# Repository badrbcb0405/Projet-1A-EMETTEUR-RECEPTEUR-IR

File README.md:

# Projet-1A-EMETTEUR-RECEPTEUR-IR

Ce depot contient les deux projets KiCad et la partie du développement informatique sur STM32 CubeIDE:

- KICAD_EMETTEUR_PCB_final (1)
- KICAD RECEPTEUR FINAL2 (2)

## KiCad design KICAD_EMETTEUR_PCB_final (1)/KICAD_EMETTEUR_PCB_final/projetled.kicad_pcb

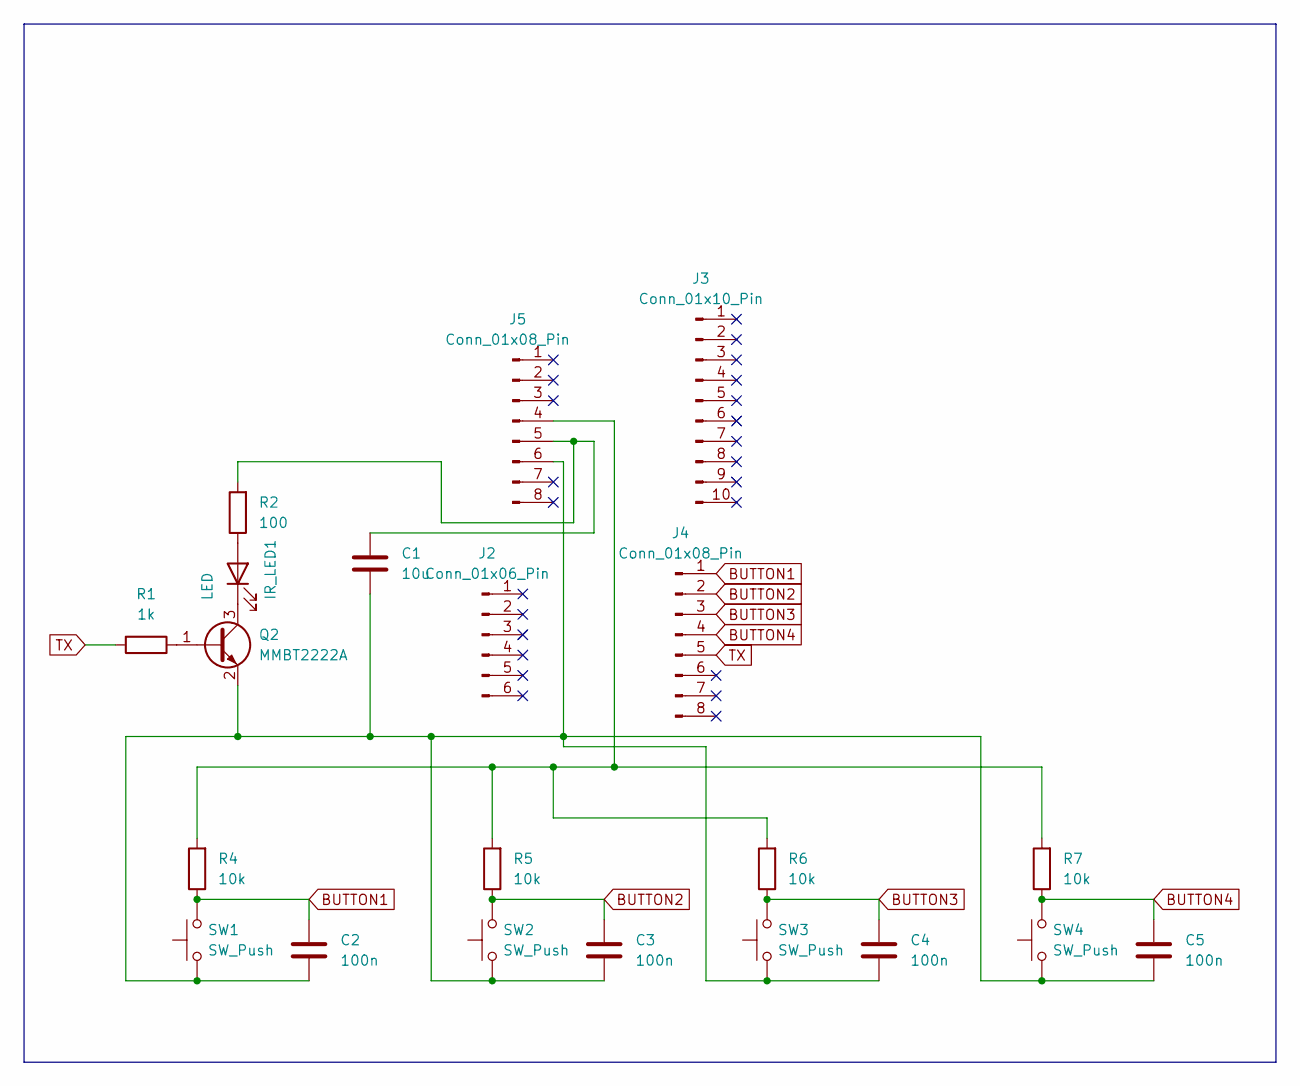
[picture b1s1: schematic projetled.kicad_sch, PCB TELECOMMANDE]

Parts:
C1: 10u; C_0805_2012Metric
C2, C3, C4, C5: 100n; C_0805_2012Metric
IR_LED1: LED; LED_D3.0mm_Horizontal_O1.27mm_Z2.0mm
J2: Conn_01x06_Pin; PinHeader_1x06_P2.54mm_Vertical
J3: Conn_01x10_Pin; PinHeader_1x10_P2.54mm_Vertical
J4, J5: Conn_01x08_Pin; PinHeader_1x08_P2.54mm_Vertical
Q2: MMBT2222A; SOT-23
R1: 1k; R_0805_2012Metric
R2: 100; R_0805_2012Metric
R4, R5, R6, R7: 10k; R_0805_2012Metric
SW1, SW2, SW3, SW4: SW_Push; SW_PUSH_6mm

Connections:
BUTTON1: C2.1, J4.1, R4.1, SW1.2
BUTTON2: C3.1, J4.2, R5.1, SW2.2
BUTTON3: C4.1, J4.3, R6.1, SW3.2
BUTTON4: C5.1, J4.4, R7.1, SW4.2
unnamed: IR_LED1.2 (A), R2.1
unnamed: IR_LED1.1 (K), Q2.3 (C)
unnamed: J5.4, R4.2, R5.2, R6.2, R7.2
unnamed: C1.1, J5.5, R2.2
unnamed: C1.2, C2.2, C3.2, C4.2, C5.2, J5.6, Q2.2 (E), SW1.1, SW2.1, SW3.1, SW4.1
unnamed: Q2.1 (B), R1.1
TX: J4.5, R1.2

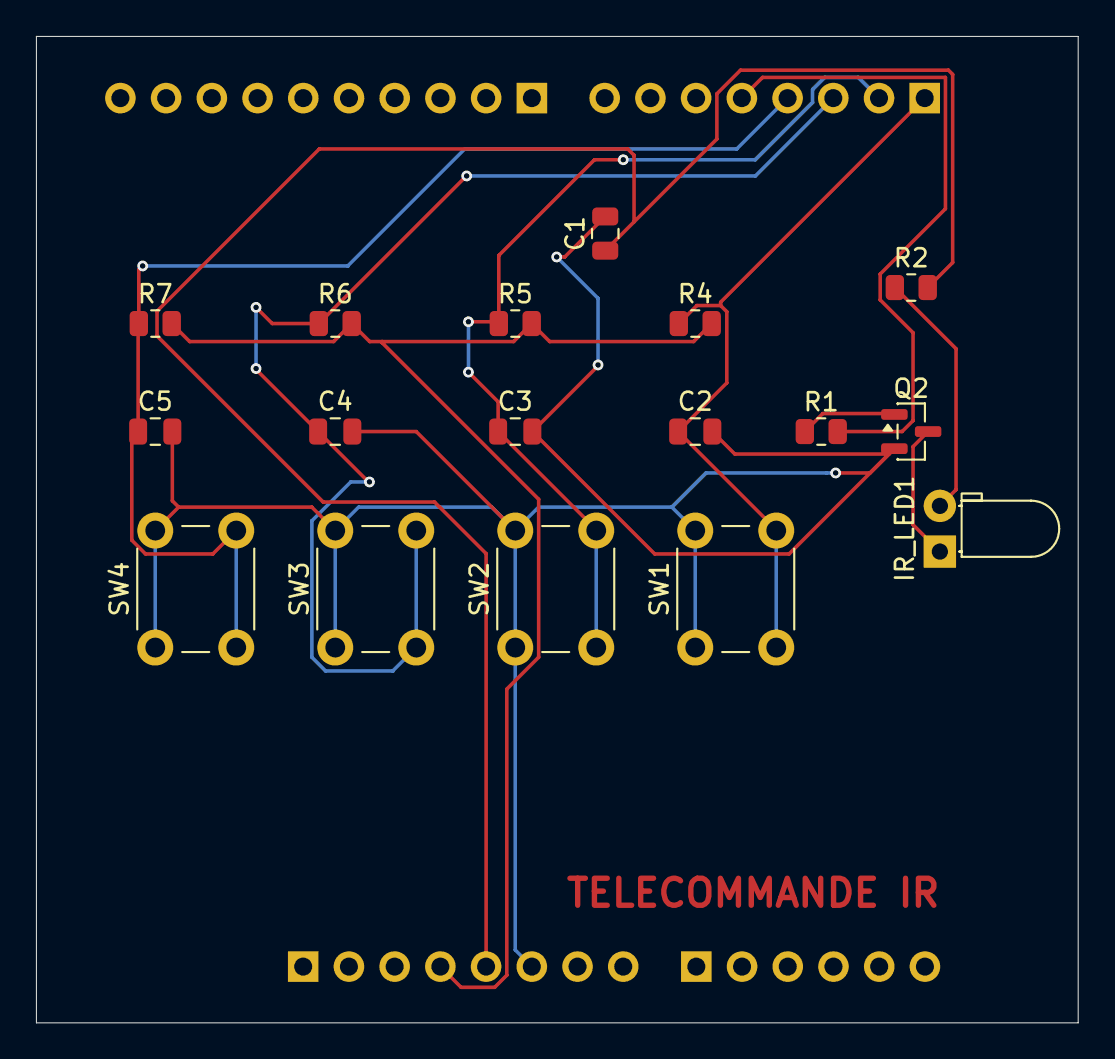
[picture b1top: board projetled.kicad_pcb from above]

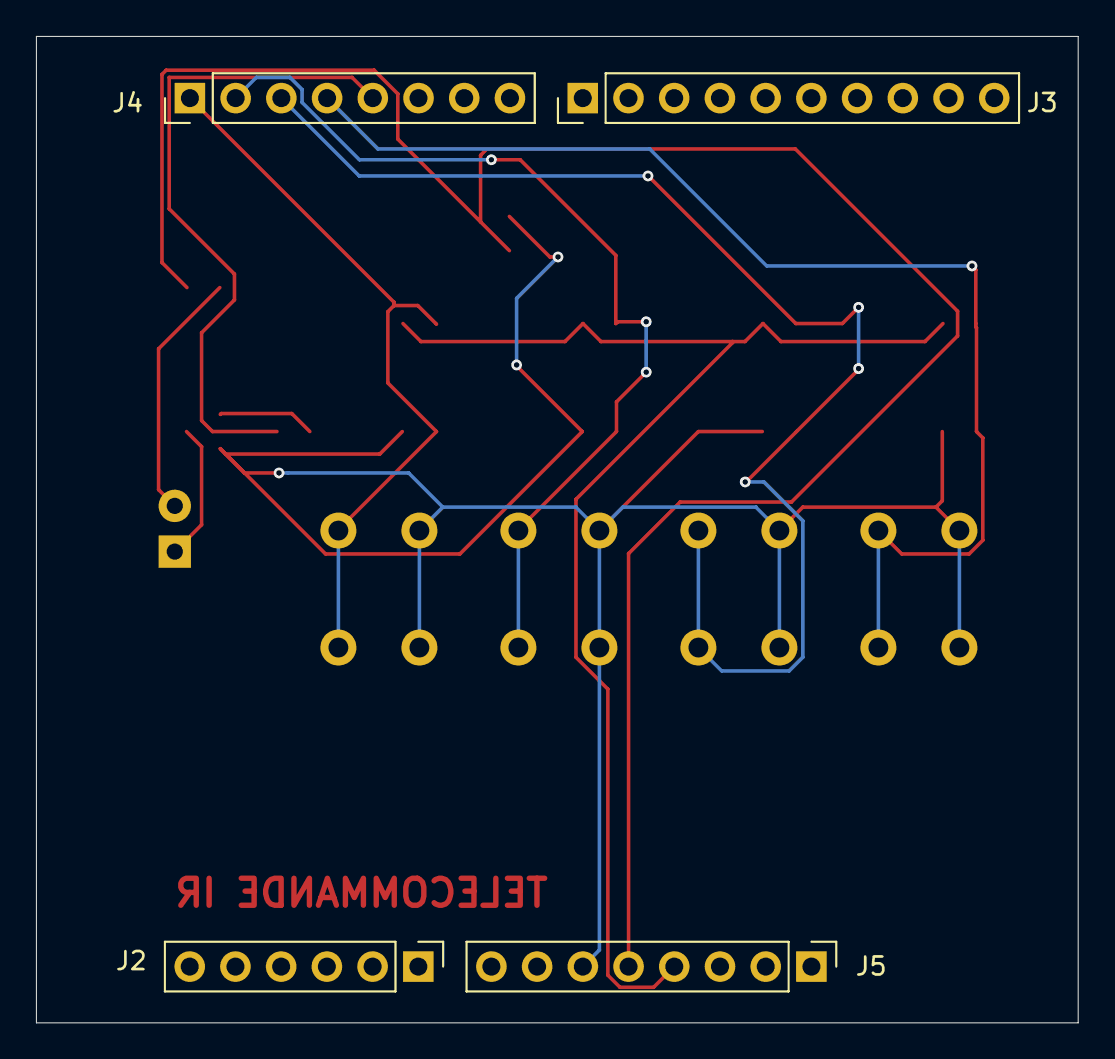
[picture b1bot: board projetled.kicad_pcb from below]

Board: 2 copper layers, 57.9 x 54.8 mm, 21 parts (4 on the bottom side), 11 nets.

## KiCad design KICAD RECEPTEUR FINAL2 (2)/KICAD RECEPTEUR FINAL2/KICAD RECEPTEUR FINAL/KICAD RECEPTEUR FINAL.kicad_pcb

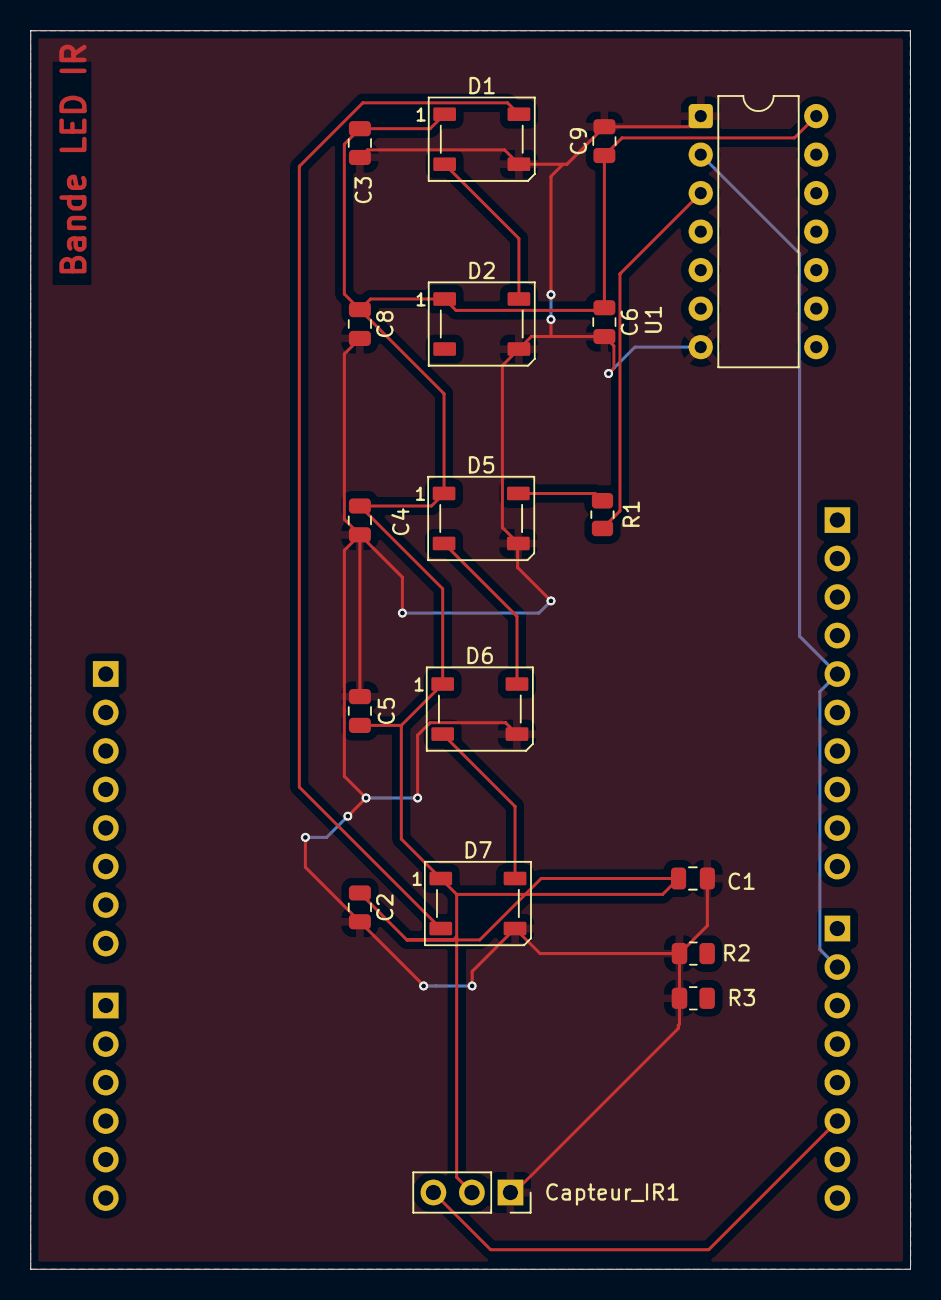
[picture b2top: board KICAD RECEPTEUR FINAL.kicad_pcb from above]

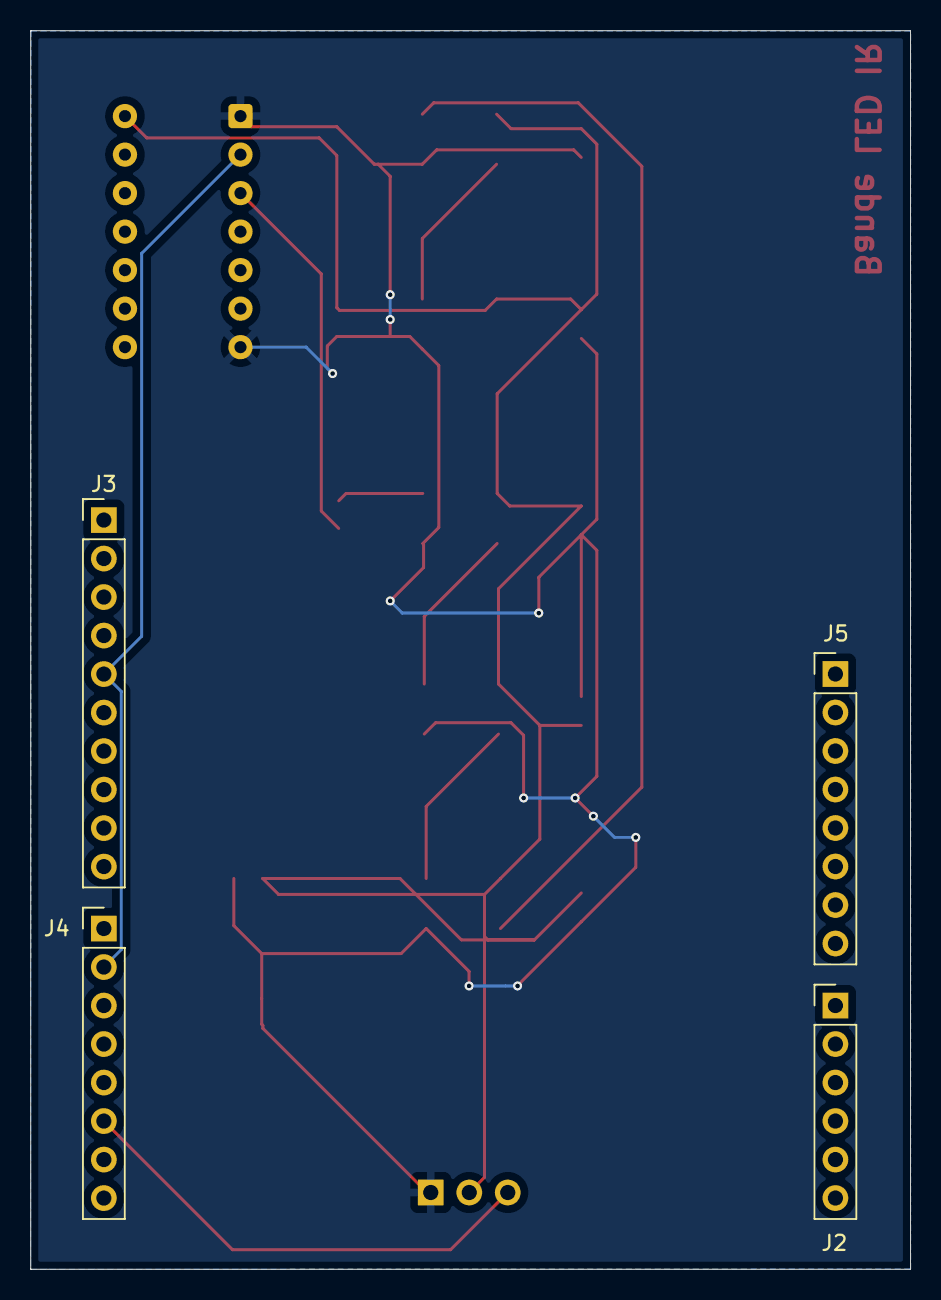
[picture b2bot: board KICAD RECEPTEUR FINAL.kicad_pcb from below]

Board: 2 copper layers, 58.0 x 81.7 mm, 22 parts (4 on the bottom side), 10 nets.

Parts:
C1: 100 n; C_0805_2012Metric
C2, C4, C5, C6, C8, C9: 100n; C_0805_2012Metric
C3: 470u; C_0805_2012Metric
Capteur_IR1: Conn_01x03; PinSocket_1x03_P2.54mm_Vertical
D1, D2, D5, D6, D7: WS2812B; LED_WS2812B_PLCC4_5.0x5.0mm_P3.2mm
J2: Conn_01x06_Pin; PinHeader_1x06_P2.54mm_Vertical
J3: Conn_01x10_Pin; PinHeader_1x10_P2.54mm_Vertical
J4, J5: Conn_01x08_Pin; PinHeader_1x08_P2.54mm_Vertical
R1: 470; R_0805_2012Metric
R2, R3: 5.1k; R_0805_2012Metric
U1: 74AHCT125; DIP-14_W7.62mm

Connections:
+5V: C1.1, C2.1, C3.1, C4.1, C5.1, C6.1, C8.1, C9.1, Capteur_IR1.2, D1.1 (VDD), D2.1 (VDD), D5.1 (VDD), D6.1 (VDD), D7.1 (VDD), U1.14 (VCC)
GND: C1.2, C2.2, C3.2, C4.2, C5.2, C6.2, C8.2, C9.2, Capteur_IR1.1, D1.3 (VSS), D2.3 (VSS), D5.3 (VSS), D6.3 (VSS), D7.3 (VSS), R2.1, R3.1, U1.1, U1.7 (GND)
unnamed: Capteur_IR1.3, J4.6
unnamed: D1.4 (DIN), D7.2 (DOUT)
unnamed: D1.2 (DOUT), D2.4 (DIN)
unnamed: D5.4 (DIN), R1.1
unnamed: D5.2 (DOUT), D6.4 (DIN)
unnamed: D6.2 (DOUT), D7.4 (DIN)
unnamed: J3.5, J4.2, U1.2
unnamed: R1.2, U1.3

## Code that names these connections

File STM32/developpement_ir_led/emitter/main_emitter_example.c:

/*
 * Exemple d'integration dans Core/Src/main.c du projet STM32CubeIDE emetteur.
 * Garde les fonctions SystemClock_Config(), MX_GPIO_Init(), MX_TIMx_Init()
 * generees par CubeMX, puis ajoute les blocs USER CODE ci-dessous.
 */

#include "main.h"
#include "app_ir_remote.h"
#include "ir_nec.h"

extern TIM_HandleTypeDef htim1; /* Timer PWM 38 kHz pour LED IR */

#define IR_REMOTE_TASK_PERIOD_MS 5u

/*
 * Exemple de mapping GPIO.
 * Les noms BUTTON1 a BUTTON4 correspondent aux labels de la carte KiCad.
 */
static const IR_ButtonMap remote_buttons[] =
{
    {BUTTON1_GPIO_Port, BUTTON1_Pin, IR_CMD_POWER},
    {BUTTON2_GPIO_Port, BUTTON2_Pin, IR_CMD_BRIGHTNESS_UP},
    {BUTTON3_GPIO_Port, BUTTON3_Pin, IR_CMD_BRIGHTNESS_DOWN},
    {BUTTON4_GPIO_Port, BUTTON4_Pin, IR_CMD_MODE},
};

static IR_Remote remote =
{
    .carrier_timer = &htim1,
    .carrier_channel = TIM_CHANNEL_1,
    .buttons = remote_buttons,
    .button_count = sizeof(remote_buttons) / sizeof(remote_buttons[0]),
    .address = IR_NEC_ADDRESS,
};

int main(void)
{
    HAL_Init();
    SystemClock_Config();

    MX_GPIO_Init();
    MX_TIM1_Init();

    IR_Remote_Init(&remote);

    while (1)
    {
        IR_Remote_Task(&remote);
        HAL_Delay(IR_REMOTE_TASK_PERIOD_MS);
    }
}

/*
 * Reglage timer PWM 38 kHz :
 *
 * Frequence_PWM = Frequence_Timer / ((PSC + 1) * (ARR + 1))
 *
 * Exemple si timer clock = 80 MHz :
 * PSC = 0
 * ARR = 2104     -> 80 MHz / 2105 = 38005 Hz
 * CCR1 = ARR / 3 -> duty cycle environ 33 %
 */

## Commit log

2026-05-29 Initial project files
